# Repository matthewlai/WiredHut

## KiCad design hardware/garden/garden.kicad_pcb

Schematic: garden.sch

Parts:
AE1: Antenna_Dipole; TI_DN007_2.4GHz
C1, C7: DNP; C_0402_1005Metric
C2: 220uF/25V; CP_Radial_D8.0mm_P3.50mm; LCSC C160181
C3, C4, C5, C8, C20: 0.1uF; C_0402_1005Metric; LCSC C1525
C6: 4.7uF; C_0402_1005Metric; LCSC C23733
C9: 10uF; C_0402_1005Metric; LCSC C15525
C10, C21: 22uF; C_0603_1608Metric; LCSC C59461
C15: 10uF; C_0805_2012Metric; LCSC C15850
C16: 0.1uF/50V; C_0603_1608Metric; LCSC C14663
D3, D7, D8, D9, D10, D11, D12, D13, D14: D_Schottky; D_SOD-123; LCSC C8598
D4, D6: RED; LED_0603_1608Metric; LCSC C72038
D5: GREEN; LED_0603_1608Metric; LCSC C72043
H1, H2, H3: MountingHole; MountingHole_3.2mm_M3
J1: CONN_01X04; JST_PH_S4B-PH-K_1x04_P2.00mm_Horizontal; LCSC C157926
J2: CONN_01X02; WJ2EDGRC-5-08-2P; LCSC C3697
J3, J4, J5, J6, J11, J12, J13: CONN_01X02; KF2EDGR-3.5-2P; LCSC C441171
J7: CONN_01X04; JST_SH_SM04B-SRSS-TB_1x04-1MP_P1.00mm_Horizontal; LCSC C437064
J8: CONN_01X04; KF2EDGR-3.5-4P; LCSC C441173
J9: USB_C_Receptacle_USB2.0; USB_C_Receptacle_HRO_TYPE-C-31-M-12; LCSC C165948
J10: CONN_01X06; PinHeader_1x06_P2.54mm_Vertical
J14, J16: CONN_01X03; JST_PH_S3B-PH-SM4-TB_1x03-1MP_P2.00mm_Horizontal; LCSC C265101
L1: 3.3uH; SWPA30xxS; LCSC C48020
LOGO1: LOGO; qwiic
LOGO2: Logo_Open_Hardware_Large; OSHW-Logo2_9.8x8mm_SilkScreen
Q1, Q4: Q_NPN_BEC; SOT-23; LCSC C2150
Q2, Q3, Q6, Q7, Q9, Q10: YJL3416A; SOT-23; LCSC C389061
Q5: Q_NMOS_GSD/60V; SOT-23; LCSC C282260
Q8: Q_PMOS_GDS; SOT-23; LCSC C113490
R1, R19: 2.2kR; R_0402_1005Metric; LCSC C25879
R2: 5mR; R_2512_6332Metric; LCSC C371096
R3, R13: 5.1k; R_0402_1005Metric; LCSC C25905
R4: 0R; R_0402_1005Metric; LCSC C17168
R5, R27, R28: 100kR; R_0402_1005Metric; LCSC C25741
R6: 6.8R; R_0402_1005Metric; LCSC C409930
R7, R14, R15, R16, R17, R18, R20, R21, R29, R30: 10kR; R_0402_1005Metric; LCSC C25744
R8, R9, R10: 100R; R_0402_1005Metric; LCSC C25076
R11, R12, R24: 1kR; R_0402_1005Metric; LCSC C11702
R22: 49.9k; R_0402_1005Metric; LCSC C25897
R23: 16.2k; R_0402_1005Metric; LCSC C27176
R25, R26: 470R; R_0402_1005Metric; LCSC C25117
SW1: SW_Push; SW_Push_1P1T_NO_5.1x5.1mm; LCSC C318887
U1: SHT30-DIS; Sensirion_DFN-8-1EP_2.5x2.5mm_P0.5mm_EP1.1x1.7mm; LCSC C77361
U2: INA3221; Texas_RGV_S-PVQFN-N16_EP2.1x2.1mm; LCSC C181255
U3: CH340C; SOIC-16_3.9x9.9mm_P1.27mm; LCSC C84681
U6: ESP32-PICO-V3; QFN-48-1EP_7x7mm_P0.5mm_EP5.3x5.3mm; LCSC C967022
U9: TPMP2359; TSOT-23-6; LCSC C2959845

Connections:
+3V3: C3.1, C4.1, C5.1, C8.1, C9.1, C10.1, C20.1, C21.1, D4.2 (A), D5.2 (A), D6.2 (A), J7.2, J8.2, J10.2, J10.5, J14.2, J16.2, L1.2, R1.1, R11.1, R12.1, R18.2, R19.1, R22.1, U1.5, U2.4, U3.4, U3.16, U6.1, U6.3, U6.4, U6.19, U6.37, U6.43, U6.46
+12V: C2.1, D3.1 (K), D8.1 (K), D9.1 (K), D11.1 (K), D12.2, D13.1 (K), D14.1 (K), J3.2, J4.2, J5.2, J11.2, J12.2, J13.2, Q8.3, R2.1, R6.2, U2.2, U2.15
/BATT_SHUNT_N: J2.2, R2.2, U2.1
/CC1: J9.A5, R3.1, R27.1
/CC1_ADC: R27.2, U6.5
/CC2: J9.B5, R13.1, R28.1
/CC2_ADC: R28.2, U6.6
/Dm: J9.A7, J9.B7, U3.6
/Dp: J9.A6, J9.B6, U3.5
/EN: C6.1, Q1.3, R18.1, SW1.1, U6.9
/GRAVITY0: J10.1, J14.3, U6.7
/GRAVITY1: J10.4, J16.3, U6.8
/IO0: Q4.3, U6.23
/LED0: R8.1, U6.33
/LED1: R9.1, U6.34
/LED2: R10.1, U6.38
/LNA: C1.1, R4.2, U6.2
/PRESSURE_SW: Q5.1, R14.2, U6.24
/PRES_SHUNT_N: J6.2, R6.1, U2.14
/SCL: R19.2, U1.4, U2.6, U6.28
/SCL_EXT: J7.4, J8.4, R12.2, U6.13
/SDA: R1.2, U1.1, U2.7, U6.27
/SDA_EXT: J7.3, J8.3, R11.2, U6.12
/SW0: Q7.1, R21.2, U6.15
/SW1: Q6.1, R20.2, U6.16
/SW2: Q3.1, R15.2, U6.17
/SW3: Q2.1, R7.2, U6.18
/SW4: Q9.1, R29.2, U6.20
/SW5: Q10.1, R30.2, U6.21
/USB_DTR: Q4.2, R16.2, U3.13
/USB_RTS: Q1.2, R17.2, U3.14
/USB_RX: R25.1, U3.3
/USB_TX: U3.2, U6.40
/VD_RX: J1.3, R26.1
/VD_TX: J1.2, U6.29
/Vbus: D10.2, J9.A4, J9.A9, J9.B4, J9.B9, R24.1
/Vbus_blocked: C15.1, D10.1, D12.1, Q8.2, R5.1, U9.5
/~Vbus_to_12V_EN: Q8.1, R24.2, U6.14
GND: AE1.1, C1.2, C2.2, C3.2, C4.2, C5.2, C6.2, C7.2, C8.2, C9.2, C10.2, C15.2, C20.2, C21.2, D7.2, J1.1, J2.1, J7.1, J8.1, J9.A1, J9.A12, J9.B1, J9.B12, J9.S1, J10.3, J10.6, J14.1, J16.1, Q2.2, Q3.2, Q5.2, Q6.2, Q7.2, Q9.2, Q10.2, R3.2, R7.1, R13.2, R14.1, R15.1, R20.1, R21.1, R23.2, R29.1, R30.1, SW1.2, U1.2, U1.7, U1.8, U1.9, U2.3, U2.5, U2.11, U2.12, U3.1, U6.49, U9.2
unnamed: AE1.2, C7.1, R4.1
unnamed: C16.1, U9.1
unnamed: C16.2, D7.1, L1.1, U9.6
unnamed: D3.2 (A), J11.1, Q6.3
unnamed: D4.1 (K), R8.2
unnamed: D5.1 (K), R9.2
unnamed: D6.1 (K), R10.2
unnamed: D8.2 (A), J4.1, Q2.3
unnamed: D9.2 (A), J5.1, Q3.3
unnamed: D11.2 (A), J12.1, Q7.3
unnamed: D13.2 (A), J3.1, Q9.3
unnamed: D14.2 (A), J13.1, Q10.3
unnamed: J6.1, Q5.3
unnamed: Q1.1, R16.1
unnamed: Q4.1, R17.1
unnamed: R5.2, U9.4
unnamed: R22.2, R23.1, U9.3
unnamed: R25.2, U6.41
unnamed: R26.2, U6.32

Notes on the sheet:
Mounting holes
USB
Auto Reset
MCU
3.3V SMPS
Power Input
Battery conn
Switched Outputs
Pressure Transducer (12V/4-20mA current loop)
Ext I2C Bus
LEDs
SmartSolar VE Direct
Current Monitors
Gravity Ports
Grounded Coplanar Wave Guide (JLC7628 Substrate): Calculator: https://spok.ca/index.php/resources/tools/99-cpwcalc H = 0.18, W=0.295, T=0.035, S=0.2, Er=4.6, Z0 = 50.05R 1mm PCB
Temperature + Humidity
Shunt full scale: 163.8mV
6.8R * 24mA = 163mV
0.005R * 32A = 163mV
Open Source Hardware

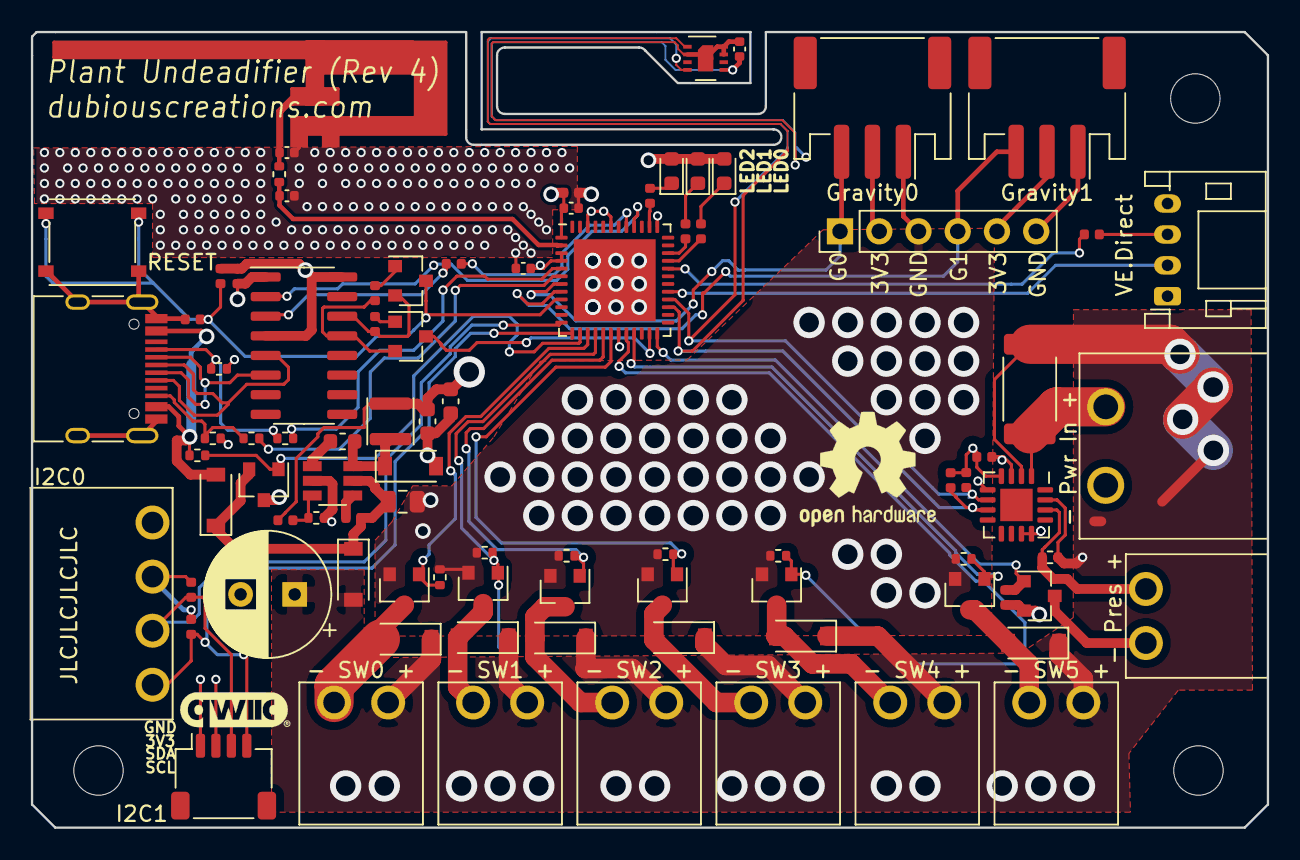
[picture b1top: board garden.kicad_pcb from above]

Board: 4 copper layers, 80.0 x 51.5 mm, 94 parts (0 on the bottom side), 58 nets.

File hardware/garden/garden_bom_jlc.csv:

"Comment","Designator","Footprint","LCSC Part #"
"220uF/25V","C2","CP_Radial_D8.0mm_P3.50mm","C160181"
"4.7uF","C6","C_0402_1005Metric","C23733"
"10uF","C9","C_0402_1005Metric","C15525"
"10uF","C15","C_0805_2012Metric","C15850"
"0.1uF/50V","C16","C_0603_1608Metric","C14663"
"0.1uF","C20,C4,C3,C5,C8","C_0402_1005Metric","C1525"
"22uF","C21,C10","C_0603_1608Metric","C59461"
"RED","D4,D6","LED_0603_1608Metric","C72038"
"GREEN","D5","LED_0603_1608Metric","C72043"
"D_Schottky","D9,D8,D7,D11,D3,D12,D10,D13,D14","D_SOD-123","C8598"
"CONN_01X04","J1","JST_PH_S4B-PH-K_1x04_P2.00mm_Horizontal","C157926"
"CONN_01X02","J2","WJ2EDGRC-5-08-2P","C3697"
"CONN_01X02","J4,J5,J6,J11,J12,J3,J13","KF2EDGR-3.5-2P","C441171"
"CONN_01X04","J7","JST_SH_SM04B-SRSS-TB_1x04-1MP_P1.00mm_Horizontal","C437064"
"CONN_01X04","J8","KF2EDGR-3.5-4P","C441173"
"USB_C_Receptacle_USB2.0","J9","USB_C_Receptacle_HRO_TYPE-C-31-M-12","C165948"
"CONN_01X03","J14,J16","JST_PH_S3B-PH-SM4-TB_1x03-1MP_P2.00mm_Horizontal","C265101"
"3.3uH","L1","SWPA30xxS","C48020"
"Q_NPN_BEC","Q1,Q4","SOT-23","C2150"
"YJL3416A","Q2,Q3,Q6,Q7,Q9,Q10","SOT-23","C389061"
"Q_NMOS_GSD/60V","Q5","SOT-23","C282260"
"Q_PMOS_GDS","Q8","SOT-23","C113490"
"5mR","R2","R_2512_6332Metric","C371096"
"5.1k","R3,R13","R_0402_1005Metric","C25905"
"0R","R4","R_0402_1005Metric","C17168"
"100kR","R5,R27,R28","R_0402_1005Metric","C25741"
"6.8R","R6","R_0402_1005Metric","C409930"
"100R","R8,R9,R10","R_0402_1005Metric","C25076"
"1kR","R11,R12,R24","R_0402_1005Metric","C11702"
"10kR","R16,R17,R18,R14,R7,R15,R20,R21,R29,R30","R_0402_1005Metric","C25744"
"2.2kR","R19,R1","R_0402_1005Metric","C25879"
"49.9k","R22","R_0402_1005Metric","C25897"
"16.2k","R23","R_0402_1005Metric","C27176"
"470R","R25,R26","R_0402_1005Metric","C25117"
"SW_Push","SW1","SW_Push_1P1T_NO_5.1x5.1mm","C318887"
"SHT30-DIS","U1","Sensirion_DFN-8-1EP_2.5x2.5mm_P0.5mm_EP1.1x1.7mm","C77361"
"INA3221","U2","Texas_RGV_S-PVQFN-N16_EP2.1x2.1mm","C181255"
"CH340C","U3","SOIC-16_3.9x9.9mm_P1.27mm","C84681"
"ESP32-PICO-V3","U6","QFN-48-1EP_7x7mm_P0.5mm_EP5.3x5.3mm","C967022"
"TPMP2359","U9","TSOT-23-6","C2959845"

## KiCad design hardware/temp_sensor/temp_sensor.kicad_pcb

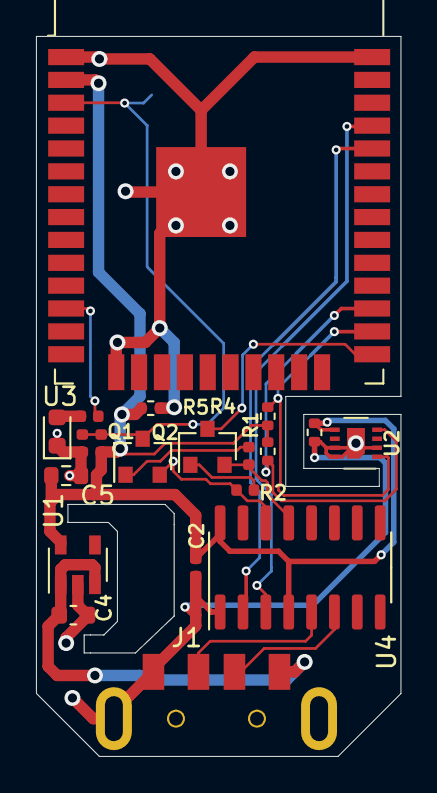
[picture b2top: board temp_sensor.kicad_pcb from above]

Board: 4 copper layers, 20.2 x 40.0 mm, 21 parts (1 on the bottom side), 17 nets.

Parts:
C1: 10uF; R_0402_1005Metric
C2, C3: 0.1uF; R_0402_1005Metric
C4, C5: 1uF; R_0603_1608Metric
C6: 4.7uF; R_0402_1005Metric
D11: Green; LED_0603_1608Metric
J1: USB_A; USB-A-XKB_U217
JP1: SolderJumper_2_Open; SolderJumper-2_P1.3mm_Open_RoundedPad1.0x1.5mm
Q1, Q2: Q_NPN_BEC; SOT-23
R1, R2, R3, R4, R5: 10kR; R_0402_1005Metric
R12: 47R; R_0402_1005Metric
U1: AP2112K-3.3; SOT-23-5
U2: SHT31-DIS; Sensirion_DFN-8-1EP_2.5x2.5mm_P0.5mm_EP1.1x1.7mm
U3: ESP32-WROOM-32
U4: CH340C; SOIC-16_3.9x9.9mm_P1.27mm

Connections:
+3V3: C1.1, C2.1, C3.1, C5.1, R3.2, R4.2, R5.2, U1.5, U2.5, U3.2, U4.4, U4.16
/EN: C6.1, JP1.1, Q1.3, R3.1, U3.3
/IO0: Q2.3, U3.25
/LED1: R12.1, U3.12
/SCL: R5.1, U2.4, U3.27
/SDA: R4.1, U2.1, U3.26
/USB_DM: J1.2, U4.6
/USB_DP: J1.3, U4.5
/USB_DTR: Q2.2, R1.2, U4.13
/USB_RTS: Q1.2, R2.2, U4.14
/USB_RX: U3.35, U4.3
/USB_TX: U3.34, U4.2
GND: C1.2, C2.2, C3.2, C4.2, C5.2, C6.2, D11.1, J1.4, J1.5, JP1.2, U1.2, U2.2, U2.7, U2.8, U2.9, U3.1, U3.15, U3.38, U3.39, U4.1
unnamed: D11.2, R12.2
unnamed: Q1.1, R1.1
unnamed: Q2.1, R2.1
VBUS: C4.1, J1.1, U1.1, U1.3

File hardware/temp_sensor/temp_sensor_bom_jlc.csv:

"Comment","Designator","Footprint","LCSC Part #"
"10uF","C1","R_0402_1005Metric","C15525"
"0.1uF","C2,C3","R_0402_1005Metric","C1525"
"1uF","C4","R_0603_1608Metric","C15849"
"22uF","C5","R_0603_1608Metric","C59461"
"4.7uF","C6","R_0402_1005Metric","C23733"
"Green","D11","LED_0603_1608Metric","C72043"
"USB_A","J1","USB-A-XKB_U217","C319178"
"Q_NPN_BEC","Q1,Q2","SOT-23","C2150"
"10kR","R1,R2,R3,R4,R5","R_0402_1005Metric","C25744"
"47R","R12","R_0402_1005Metric","C25118"
"AZ1117-3.3","U1","SOT-223-3_TabPin2","C92102"
"SHT31-DIS","U2","Sensirion_DFN-8-1EP_2.5x2.5mm_P0.5mm_EP1.1x1.7mm","C80862"
"ESP32-WROOM-32","U3","ESP32-WROOM-32","C473012"
"CH340C","U4","SOIC-16_3.9x9.9mm_P1.27mm","C84681"

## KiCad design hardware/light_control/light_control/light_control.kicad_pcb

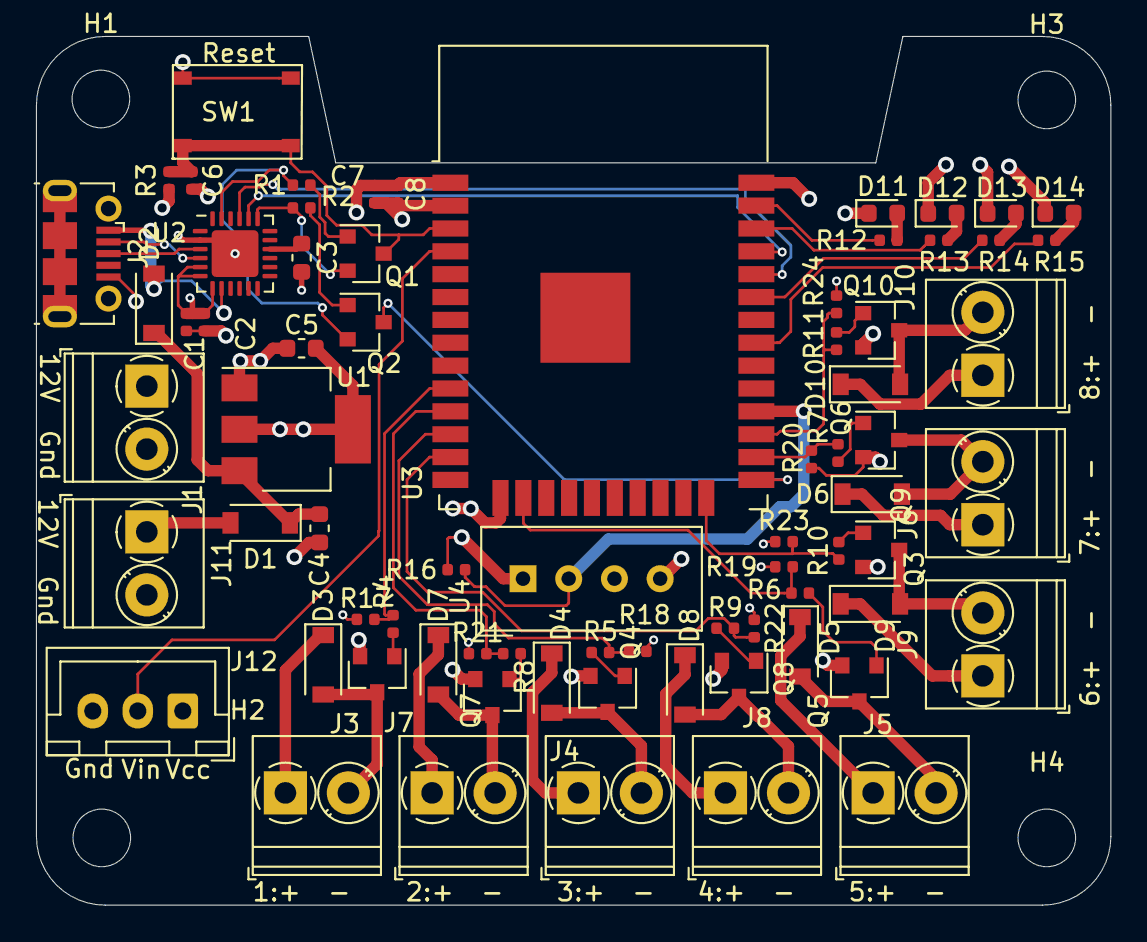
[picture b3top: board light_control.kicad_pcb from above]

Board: 4 copper layers, 59.7 x 48.3 mm, 77 parts (0 on the bottom side), 50 nets.

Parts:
C1: 1uF; R_0402_1005Metric
C2, C6, C8: 0.1uF; R_0402_1005Metric
C3: 4.7uF; R_0603_1608Metric
C4: 1uF; R_0603_1608Metric
C5: 22uF; R_0603_1608Metric
C7: 10uF; R_0402_1005Metric
D1, D2, D3, D4, D5, D6, D7, D8, D9, D10: D_Schottky; D_SOD-123
D11, D12: Green; LED_0603_1608Metric
D13, D14: Red; LED_0603_1608Metric
H1, H2, H3, H4: MountingHole; MountingHole_3.2mm_M3
J1, J3, J4, J5, J6, J7, J8, J9, J10, J11: Screw_Terminal_01x02; TerminalBlock_Phoenix_PT-1,5-2-3.5-H_1x02_P3.50mm_Horizontal
J2: USB_B_Micro; USB_Micro-B_Molex-105017-0001
J12: Conn_01x03; JST_XH_B3B-XH-A_1x03_P2.50mm_Vertical
Q1, Q2: Q_NPN_BEC; SOT-23
Q3: Q_NMOS_GSD; SOT-23
Q4, Q5, Q6, Q7, Q8, Q9, Q10: Q_NMOS_GDS; SOT-23
R1, R2, R3, R16, R17, R18, R19, R20, R21, R22, R23, R24: 10kR; R_0402_1005Metric
R4, R5, R6, R7, R8, R9, R10, R11: 100R; R_0402_1005Metric
R12, R13: 47R; R_0402_1005Metric
R14, R15: 150R; R_0402_1005Metric
SW1: SW_Push; TS-1187A
U1: AZ1117-3.3; SOT-223-3_TabPin2
U2: CP2104; QFN-24-1EP_4x4mm_P0.5mm_EP2.6x2.6mm
U3: ESP32-WROOM-32
U4: DHT11; Aosong_DHT11_5.5x12.0_P2.54mm

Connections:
+3V3: C1.1, C2.1, C5.1, C7.1, C8.1, R3.2, R16.2, U1.2, U2.5, U2.6, U2.7, U3.2, U4.1
/CH_1: R4.2, R17.2, U3.10
/CH_2: R8.2, R21.2, U3.11
/CH_3: R5.2, R18.2, U3.12
/CH_4: R9.2, R22.2, U3.13
/CH_5: R6.2, R19.2, U3.16
/CH_6: R10.2, R23.2, U3.24
/CH_7: R7.2, R20.2, U3.26
/CH_8: R11.2, R24.2, U3.27
/DHT_IO: R16.1, U3.28, U4.2
/EN: C6.1, Q1.3, R3.1, SW1.2, U3.3
/IO0: Q2.3, U3.25
/LED1: R12.1, U3.37
/LED2: R13.1, U3.36
/LED3: R14.1, U3.33
/LED4: R15.1, U3.31
/PIR_A: J12.2, U3.4
/USB_DM: J2.2, U2.4
/USB_DP: J2.3, U2.3
/USB_DTR: Q2.2, R1.2, U2.23
/USB_RTS: Q1.2, R2.2, U2.19
/USB_RX: U2.20, U3.35
/USB_TX: U2.21, U3.34
GND: C1.2, C2.2, C3.2, C4.2, C5.2, C6.2, C7.2, C8.2, D11.1, D12.1, D13.1, D14.1, J1.2, J2.5, J2.6, J11.2, J12.3, Q3.2, Q4.2, Q5.2, Q6.2, Q7.2, Q8.2, Q9.2, Q10.2, R17.1, R18.1, R19.1, R20.1, R21.1, R22.1, R23.1, R24.1, SW1.1, U1.1, U2.2, U2.25, U3.1, U3.15, U3.38, U4.4
unnamed: C3.1, U2.16
unnamed: C4.1, D1.1, D2.1, U1.3
unnamed: D3.2, J3.2, Q3.3
unnamed: D4.2, J4.2, Q4.3
unnamed: D5.2, J5.2, Q5.3
unnamed: D6.2, J6.2, Q6.3
unnamed: D7.2, J7.2, Q7.3
unnamed: D8.2, J8.2, Q8.3
unnamed: D9.2, J9.2, Q9.3
unnamed: D10.2, J10.2, Q10.3
unnamed: D11.2, R12.2
unnamed: D12.2, R13.2
unnamed: D13.2, R14.2
unnamed: D14.2, R15.2
unnamed: Q1.1, R1.1
unnamed: Q2.1, R2.1
unnamed: Q3.1, R4.1
unnamed: Q4.1, R5.1
unnamed: Q5.1, R6.1
unnamed: Q6.1, R7.1
unnamed: Q7.1, R8.1
unnamed: Q8.1, R9.1
unnamed: Q9.1, R10.1
unnamed: Q10.1, R11.1
VBUS: D2.2, J2.1, U2.8
VCC: D1.2, D3.1, D4.1, D5.1, D6.1, D7.1, D8.1, D9.1, D10.1, J1.1, J3.1, J4.1, J5.1, J6.1, J7.1, J8.1, J9.1, J10.1, J11.1, J12.1

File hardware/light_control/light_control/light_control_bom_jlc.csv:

"Comment","Designator","Footprint","LCSC Part #"
"1uF","C1","R_0402_1005Metric","C52923"
"0.1uF","C2,C8,C6","R_0402_1005Metric","C1525"
"4.7uF","C3","R_0603_1608Metric","C19666"
"1uF","C4","R_0603_1608Metric","C15849"
"22uF","C5","R_0603_1608Metric","C59461"
"10uF","C7","R_0402_1005Metric","C15525"
"D_Schottky","D1,D2,D3,D7,D4,D8,D5,D9,D10,D6","D_SOD-123","C8598"
"Green","D11,D12","LED_0603_1608Metric","C72043"
"Red","D13,D14","LED_0603_1608Metric","C2286"
"Q_NPN_BEC","Q1,Q2","SOT-23","C2150"
"Q_NMOS_GSD","Q3","SOT-23","C20917"
"Q_NMOS_GDS","Q7,Q4,Q8,Q5,Q9,Q6,Q10","SOT-23","C20917"
"10kR","R1,R2,R3,R16,R17,R21,R18,R22,R19,R23,R20,R24","R_0402_1005Metric","C25744"
"100R","R4,R8,R5,R9,R6,R10,R7,R11","R_0402_1005Metric","C25076"
"47R","R13,R12","R_0402_1005Metric","C25118"
"150R","R14,R15","R_0402_1005Metric","C25082"
"SW_Push","SW1","TS-1187A","C318888"
"AZ1117-3.3","U1","SOT-223-3_TabPin2","C92102"
"CP2104","U2","QFN-24-1EP_4x4mm_P0.5mm_EP2.6x2.6mm","C47742"

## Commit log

2019-05-26 Initial commit of garden PCB (copy of Ostrich)
2019-05-27 Removed .lib from gitignore (KiCAD symbol libraries should be committed)
2019-05-27 Added missing .lib files
2019-05-27 Designed garden controller
2019-05-28 Updated garden controller with test points and back emf diodes
2019-05-28 Added gnd testpoint, changed SOT footprints to hand-solder version, added PCB layout PDF
2019-05-29 Started controller impl
2019-05-29 Cosmetic changes and added fab files
2019-05-30 Implemented HTTP server
2019-05-30 Refactoring, implemented HTTP GET delegation, started implementing stub for garden MCU
2019-05-31 Added paste layer dxf
2019-06-01 Refactored remote handler code into its own class
2019-06-03 Added WIP web server dynamic value support
2019-06-03 Improved AJAX update handling
2019-06-04 Firmware WIP
2019-06-04 Refactored remote handler to support multiple clients, and DynamicVar improvements
2019-06-05 Garden firmware WIP
2019-06-07 Firmware fixes
2019-06-07 Added sqlite logging and finished implementing garden controller
2019-06-09 Added dht22 raspberry pi temp/humidity client
2019-06-11 Added TLS support and refactored config management
2019-06-11 Reduced paste layer shrinkage
2019-06-11 Improved KeyboardInterrupt handling
2019-06-16 Implemented charting and data decimation in SQL
2019-06-16 Fixed garden stat types and cosmetic changes
2019-06-16 Fixed division by zero in aggregation
2019-06-16 Javascript performance optimisations
2019-07-10 Lowered MCU clock to 24MHz
2019-07-10 Refactored ESP8266 update code, and fixed forced state not updating pump_on
2019-07-10 Added water level sensor power gating, and refactored execution throttler
2019-07-10 Improved SOC estimation
2019-07-10 Removed watering on startup
2019-07-10 Fixed garden battery SOC scaling
2019-07-10 Added garden error codes
2019-07-10 Updated AJAX update frequency
2019-09-01 Tuned timer constants and sensor power gating
2019-10-15 Added light control PCB
2019-10-23 Updated 3V3 regulator part number
2020-02-02 Add quantity column to jlc bom
2020-02-02 Add kitspace.yaml
2020-03-26 Updated hardware
2020-05-03 Added tools for working with ESP32 MicroPython
2020-08-04 Added second gen garden board
2020-08-04 Added config.py to gitignore
2020-08-04 Added old fishtank light firmware
2020-08-08 Deleted old fish tank firmware
2020-08-08 Added new fish light firmware
2020-08-08 Removed MicroPython tools for ESP32
2020-08-08 Light control PCB file format update
2020-08-14 Increased ESP32 bootloading cap to 4.7uF
2020-08-14 Renamed fishtank light firmware directory
2020-08-14 Added garden and temp sensor firmware
2020-08-16 Fixed VE.Direct pinout
2020-08-16 Undid temp sensor test change
2020-08-18 No functional change
2020-08-18 Added garden v2 firmware
2020-08-18 Updated firmware
2020-08-18 Tuned pressure sensor turn on and read delay
2020-08-18 Increased UART buffer size
2020-08-18 Disabled charge pump to save some power (the sensor seems to work fine on 12V). Added 30 seconds delay on boot for OTA.
2020-08-20 * Activated WDT * Remember battery SoC estimate in NVS * Improved solar data error handling * Added better logging for calls that take longer than estimated
2020-08-20 Implemented low water cutout
2020-08-22 Fixed coulomb counting reset using scaled values
2020-08-22 Switch main code to use renamed function
2020-09-18 Improved soil moisture scaling and linked it to sensor
2020-09-28 Improved wifi handling and reverted debug change
2020-10-04 Changed watering controller constants
2020-10-04 Added WDT to temp sensor
2021-05-23 Added WDT for temp sensor
2021-05-23 Updated fish light on time
2021-05-23 Disabled soil moisture sensor
2021-06-13 Added v3 garden controller hardware
2021-06-13 Removed stray file
2021-07-09 Updated garden and temp sensor hw
2022-07-23 Updated garden controller hardware to version 4
2022-08-02 Moved garden controller to new project
2024-10-14 Removed web controller
